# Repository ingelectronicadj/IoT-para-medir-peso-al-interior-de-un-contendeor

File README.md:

# IoT-para-medir-peso-al-interior-de-un-contendeor
Este proyecto de software y hardware emplea un modulo de comunicaciones GSM para permitir que el sensado de peso (Sensor: FSR + Microcontrolador: Atmega 328) sea enviado a un servidor de manera remota.  
Se expone graficamente el comportamiento de la celda FSR, sus diferentes configuraciónes esquematicas y se obtienen ecuaciones para la calibración adecuada del sensor haciendo uso de las curvas de fabricante y las curvas con los datos experimentales.  
A cada microcontrolador se le asignada una direccion IMEI(Asociada a la simCard empleada) como token para detectar los niveles minimos de un usuario asociado a uno ó multiples dispositivo. La placa PCB es diseñada con Eagle(Versión académica).

## Regresion Polinomial

## Diseño de circuito impreso

## WebSite de prueba

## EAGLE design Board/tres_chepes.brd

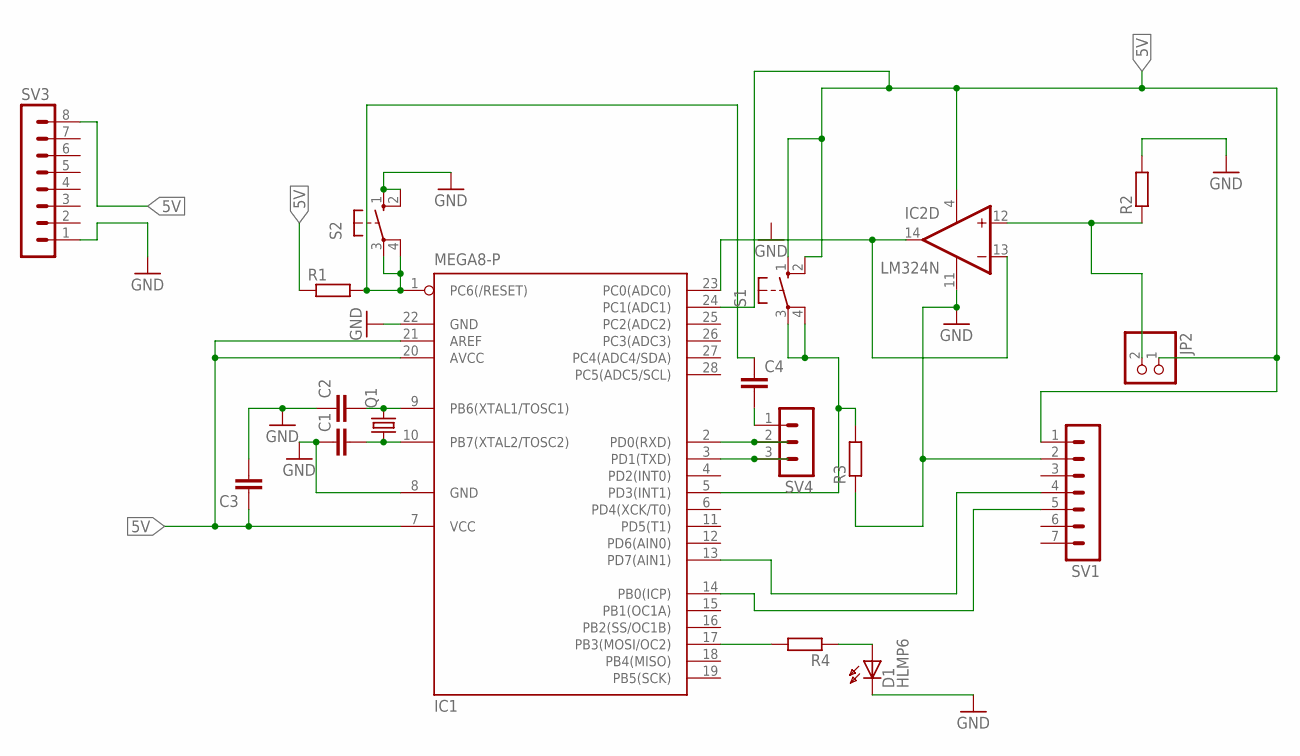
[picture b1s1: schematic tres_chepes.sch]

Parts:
C1, C2, C3: C2,5-3; C2.5-3
C4: C-EU025-024X044; C025-024X044
D1: HLMP6
IC1: MEGA8-P; DIL28-3
IC2: LM324N; DIL14
JP2: PINHD-1X2; 1X02
Q1: CRYSTALTC26V; TC26V
R1, R2, R3, R4: R-EU_0204/5; 0204/5
S1, S2: 10-XX; B3F-10XX
SV1: MA07-1
SV3: MA08-1W
SV4: MA03-1

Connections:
5V: C3.1, IC1.7 (VCC), IC1.20 (AVCC), IC1.21 (AREF), IC1.24 (PC1(ADC1)), IC2.4 (V+), JP2.1, R1.1, S1.1 (S), S1.2 (S1), SV1.1, SV3.8
GND: C1.1, C2.1, C3.2, D1.K, IC1.8 (GND), IC1.22 (GND), IC2.11 (V-), R2.2, R3.1, S2.1 (S), S2.2 (S1), SV1.2, SV3.1
unnamed: IC2.12 (+IN), JP2.2, R2.1
unnamed: C4.2, SV4.1
unnamed: IC1.17 (PB3(MOSI/OC2)), R4.2
unnamed: IC1.5 (PD3(INT1)), R3.2, S1.3, S1.4 (P1)
unnamed: IC1.3 (PD1(TXD)), SV4.3
unnamed: D1.A, R4.1
unnamed: IC1.2 (PD0(RXD)), SV4.2
unnamed: IC1.13 (PD7(AIN1)), SV1.4
unnamed: IC1.14 (PB0(ICP)), SV1.5
unnamed: C2.2, IC1.9 (PB6(XTAL1/TOSC1)), Q1.2
unnamed: C1.2, IC1.10 (PB7(XTAL2/TOSC2)), Q1.1
unnamed: C4.1, IC1.1 (PC6(/RESET)), R1.2, S2.3, S2.4 (P1)
unnamed: IC1.23 (PC0(ADC0)), IC2.13 (-IN), IC2.14 (OUT)

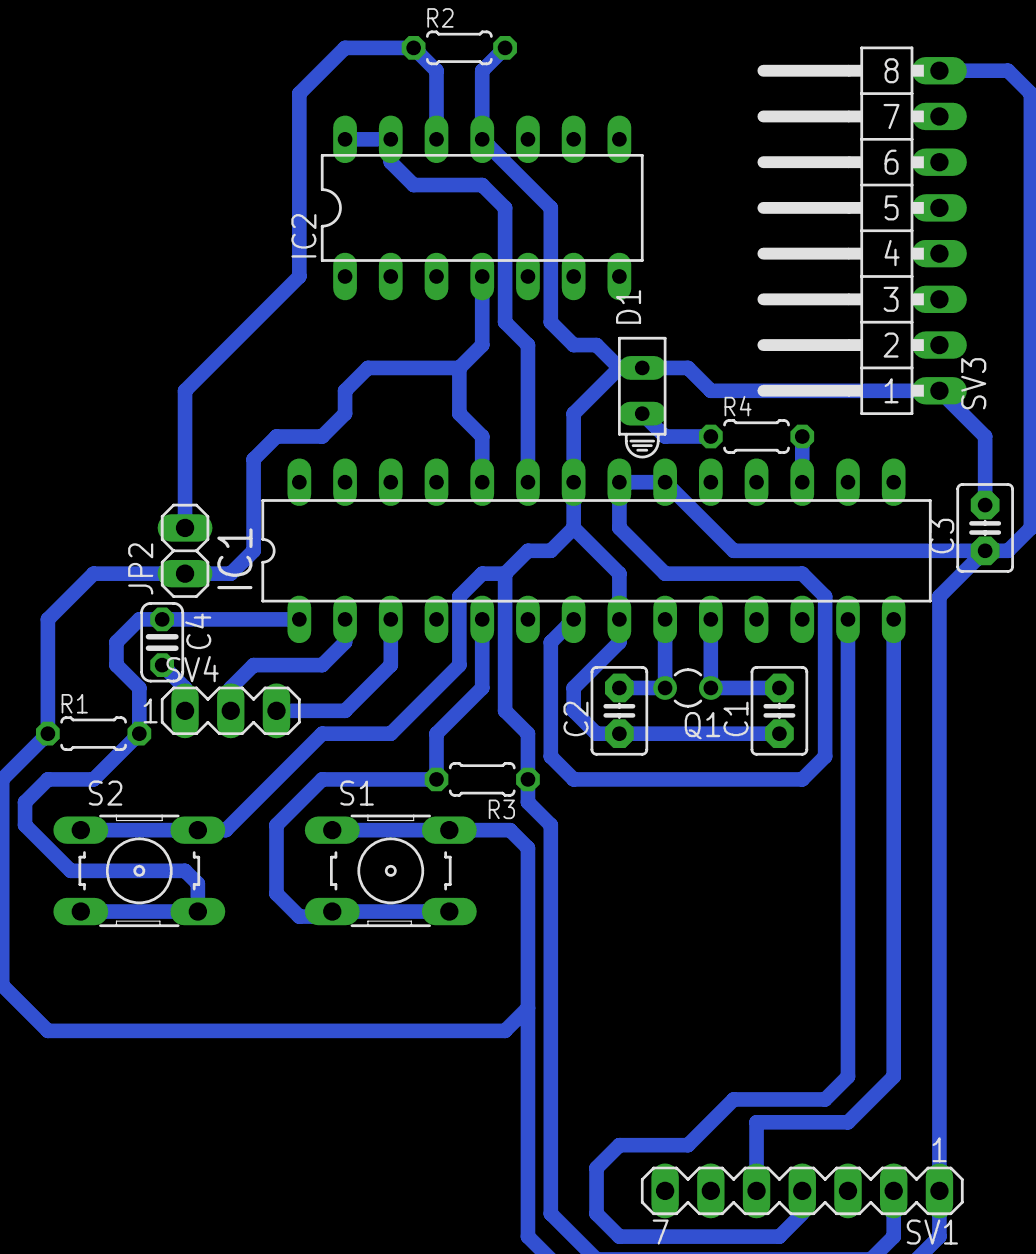
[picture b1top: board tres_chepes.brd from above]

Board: 2 copper layers, 18 parts (0 on the bottom side), 15 nets.

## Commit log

2016-11-02 Se libera version 1.0 del sistema IoT para medir peso al interior de un contenedor
2016-11-02 Se emplea libreria Timmer para enviar el peso automaticamente de acuerdo a un lapso definido de tiempo (horas, min, seg)
2016-11-02 Se elimina nexo a la wiki de bitbucket dado que se inicia versionamiento en pro de mejoras
